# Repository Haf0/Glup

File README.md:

# Glup
Glup is split keyboard 3x6 with 3 thumb cluster that support Choc and MX,and reversible pcb
there's 2 version of glup, big and little glup, big without snapable pcb and little with snappable pcb

why glup? dunno, the name is not fixed but that's the name that I just came out with hehhe

## WARNING!!!!
Untested board, please use it with your own risk!!
and I need to fix the spacing

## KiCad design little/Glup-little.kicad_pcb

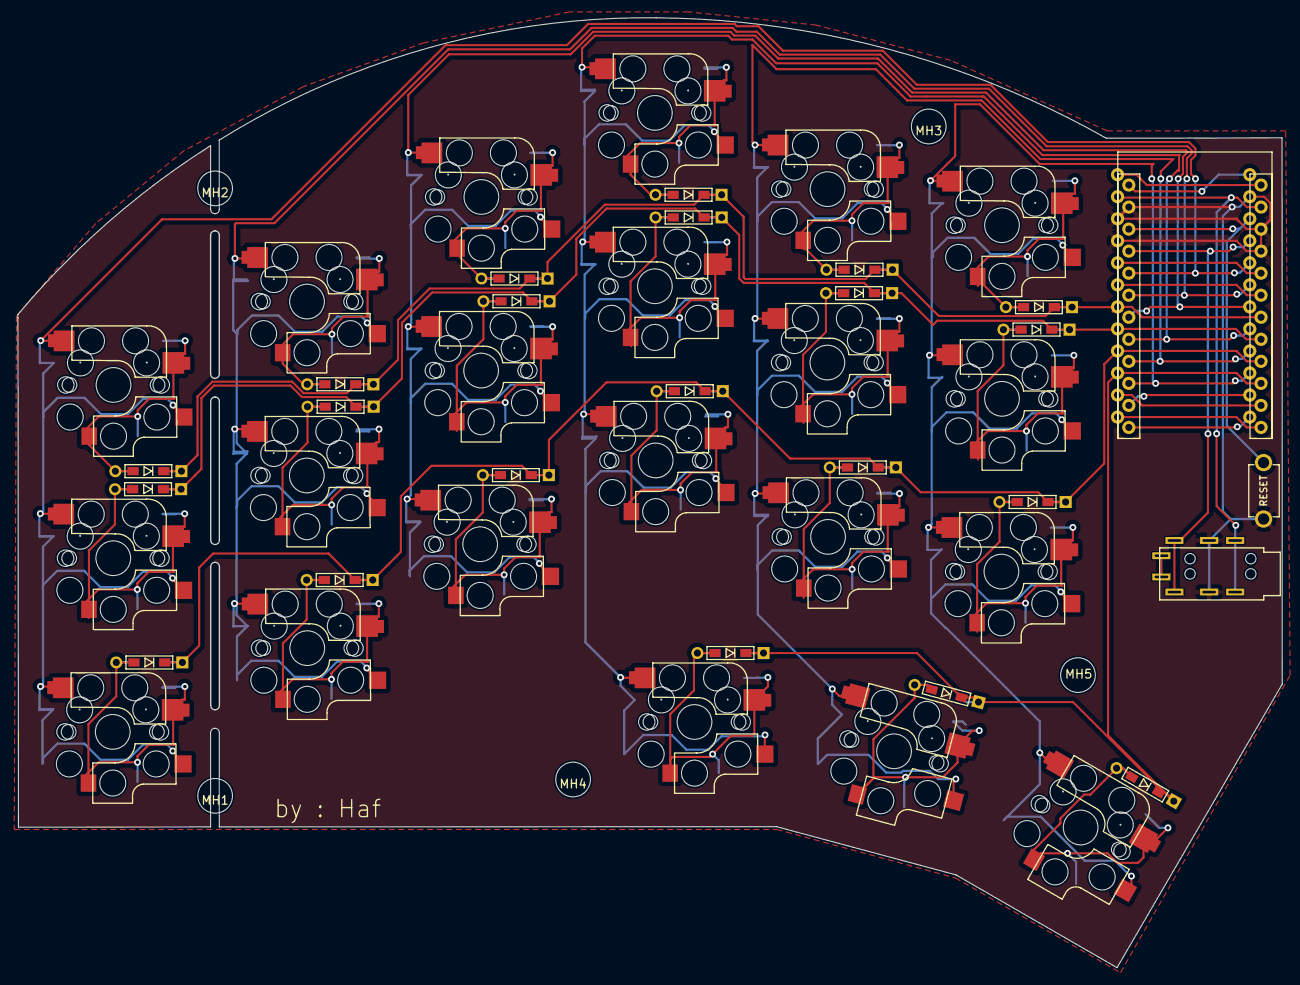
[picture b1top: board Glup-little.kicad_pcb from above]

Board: 2 copper layers, 145.7 x 109.5 mm, 50 parts (0 on the bottom side), 35 nets.

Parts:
D1, D2, D3, D4, D5, D6, D7, D8, D9, D10, D11, D12, D13, D14, D15, D16, D17, D18, D19, D20, D21: D; D3_TH_SMD
J2: MJ-4PP-9; TRRS_JACK_MJ4PP9
MH1, MH2, MH3, MH4, MH5: MOUNT_HOLE; M2_Hole_NPTH_Outside
RSW1: SW_PUSH; TACT_SWITCH_TVBP06
SW1, SW2, SW3, SW4, SW5, SW6, SW7, SW8, SW9, SW10, SW11, SW12, SW13, SW14, SW15, SW16, SW17, SW18, SW19, SW20, SW21: SW_PUSH; MX_Choc_Hotswap
U1: ProMicro; ProMicro_rev2

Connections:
GND: J2.C, RSW1.2, U1.3 (GND), U1.4 (GND), U1.23 (GND)
unnamed: D1.2 (A), SW1.2
unnamed: D2.2 (A), SW2.2
unnamed: D3.2 (A), SW3.2
unnamed: D4.2 (A), SW4.2
unnamed: D5.2 (A), SW5.2
unnamed: D6.2 (A), SW6.2
unnamed: D7.2 (A), SW7.2
unnamed: D8.2 (A), SW8.2
unnamed: D9.2 (A), SW9.2
unnamed: D10.2 (A), SW10.2
unnamed: D11.2 (A), SW11.2
unnamed: D12.2 (A), SW12.2
unnamed: D13.2 (A), SW13.2
unnamed: D14.2 (A), SW14.2
unnamed: D15.2 (A), SW15.2
unnamed: D16.2 (A), SW16.2
unnamed: D17.2 (A), SW17.2
unnamed: D18.2 (A), SW18.2
unnamed: D19.2 (A), SW19.2
unnamed: D20.2 (A), SW20.2
unnamed: D21.2 (A), SW21.2
VCC: J2.D, U1.21 (VCC)
col0: SW1.1, SW2.1, SW3.1, U1.20 (F4/A3)
col1: SW4.1, SW5.1, SW6.1, U1.19 (F5/A2)
col2: SW7.1, SW8.1, SW9.1, U1.18 (F6/A1)
col3: SW10.1, SW11.1, SW12.1, SW13.1, U1.17 (F7/A0)
col4: SW14.1, SW15.1, SW16.1, SW17.1, U1.16 (B1/15)
col5: SW18.1, SW19.1, SW20.1, SW21.1, U1.15 (B3/14)
data: J2.B, U1.2 (RX1/D2)
reset: RSW1.1, U1.22 (RST)
row0: D1.1 (K), D4.1 (K), D7.1 (K), D10.1 (K), D14.1 (K), D18.1 (K), U1.7 (4/D4)
row1: D2.1 (K), D5.1 (K), D8.1 (K), D11.1 (K), D15.1 (K), D19.1 (K), U1.8 (5/C6)
row2: D3.1 (K), D6.1 (K), D9.1 (K), D12.1 (K), D16.1 (K), D20.1 (K), U1.9 (6/D7)
row3: D13.1 (K), D17.1 (K), D21.1 (K), U1.10 (7/E6)

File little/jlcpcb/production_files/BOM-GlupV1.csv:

Comment,Designator,Footprint,LCSC
SW_PUSH,SW9,MX_Choc_Hotswap,
SW_PUSH,SW13,MX_Choc_Hotswap,
D,D14,D3_TH_SMD,
SW_PUSH,RSW1,TACT_SWITCH_TVBP06,
ProMicro,U1,ProMicro_rev2,
D,D16,D3_TH_SMD,
MOUNT_HOLE,MH1,M2_Hole_NPTH_Outside,
MOUNT_HOLE,MH2,M2_Hole_NPTH_Outside,
SW_PUSH,SW6,MX_Choc_Hotswap,
SW_PUSH,SW5,MX_Choc_Hotswap,
D,D11,D3_TH_SMD,
SW_PUSH,SW4,MX_Choc_Hotswap,
D,D20,D3_TH_SMD,
D,D13,D3_TH_SMD,
D,D7,D3_TH_SMD,
D,D1,D3_TH_SMD,
SW_PUSH,SW11,MX_Choc_Hotswap,
SW_PUSH,SW3,MX_Choc_Hotswap,
D,D17,D3_TH_SMD,
MOUNT_HOLE,MH4,M2_Hole_NPTH_Outside,
SW_PUSH,SW20,MX_Choc_Hotswap,
D,D9,D3_TH_SMD,
D,D5,D3_TH_SMD,
SW_PUSH,SW15,MX_Choc_Hotswap,
SW_PUSH,SW8,MX_Choc_Hotswap,
SW_PUSH,SW12,MX_Choc_Hotswap,
D,D19,D3_TH_SMD,
D,D21,D3_TH_SMD,
D,D8,D3_TH_SMD,
MOUNT_HOLE,MH3,M2_Hole_NPTH_Outside,
SW_PUSH,SW2,MX_Choc_Hotswap,
D,D4,D3_TH_SMD,
MOUNT_HOLE,MH5,M2_Hole_NPTH_Outside,
SW_PUSH,SW17,MX_Choc_Hotswap,
D,D10,D3_TH_SMD,
SW_PUSH,SW19,MX_Choc_Hotswap,
D,D12,D3_TH_SMD,
MJ-4PP-9,J2,TRRS_JACK_MJ4PP9,
SW_PUSH,SW18,MX_Choc_Hotswap,
SW_PUSH,SW10,MX_Choc_Hotswap,
SW_PUSH,SW21,MX_Choc_Hotswap,
D,D2,D3_TH_SMD,
D,D18,D3_TH_SMD,
SW_PUSH,SW14,MX_Choc_Hotswap,
D,D3,D3_TH_SMD,
D,D6,D3_TH_SMD,
D,D15,D3_TH_SMD,
SW_PUSH,SW16,MX_Choc_Hotswap,
SW_PUSH,SW7,MX_Choc_Hotswap,
SW_PUSH,SW1,MX_Choc_Hotswap,

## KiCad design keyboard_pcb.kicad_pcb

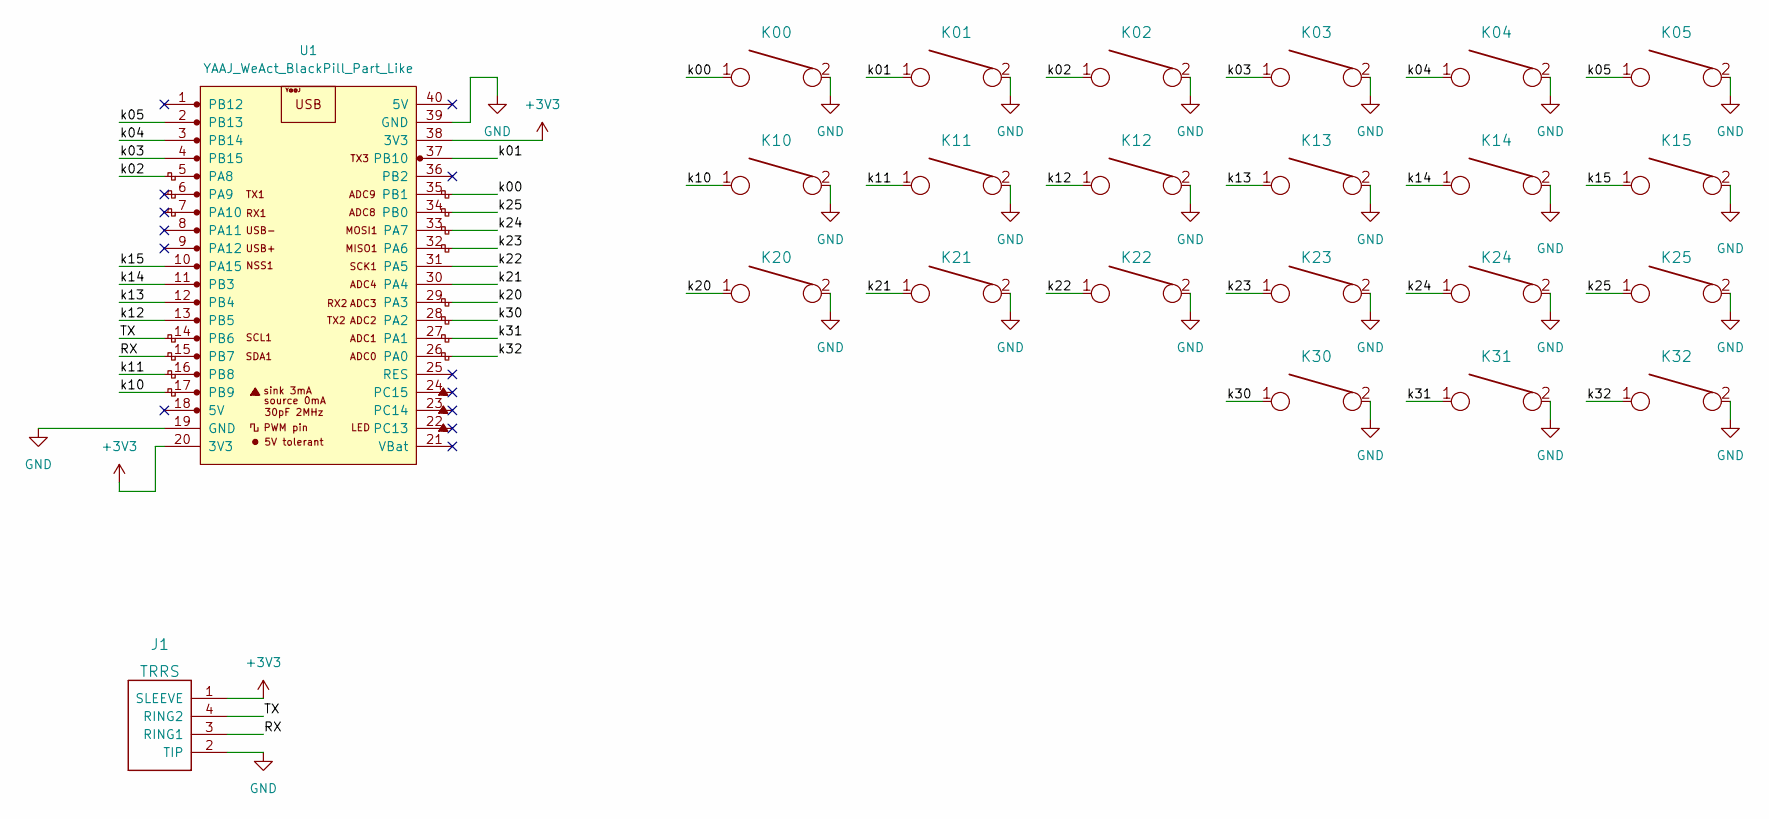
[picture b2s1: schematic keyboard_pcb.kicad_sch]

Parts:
J1: TRRS; TRRS-PJ-320A
K00, K01, K02, K03, K04, K05, K10, K11, K12, K13, K14, K15, K20, K21, K22, K23, K24, K25, K30, K31, K32: KEYSW; MX_Choc_Hotswap_Mod
U1: YAAJ_WeAct_BlackPill_Part_Like; YAAJ_WeAct_BlackPill_2

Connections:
+3V3: J1.1 (SLEEVE), U1.20 (3V3), U1.38 (3V3)
/RX: J1.3 (RING1), U1.15 (PB7)
/TX: J1.4 (RING2), U1.14 (PB6)
/k00: K00.1, U1.35 (PB1)
/k01: K01.1, U1.37 (PB10)
/k02: K02.1, U1.5 (PA8)
/k03: K03.1, U1.4 (PB15)
/k04: K04.1, U1.3 (PB14)
/k05: K05.1, U1.2 (PB13)
/k10: K10.1, U1.17 (PB9)
/k11: K11.1, U1.16 (PB8)
/k12: K12.1, U1.13 (PB5)
/k13: K13.1, U1.12 (PB4)
/k14: K14.1, U1.11 (PB3)
/k15: K15.1, U1.10 (PA15)
/k20: K20.1, U1.29 (PA3)
/k21: K21.1, U1.30 (PA4)
/k22: K22.1, U1.31 (PA5)
/k23: K23.1, U1.32 (PA6)
/k24: K24.1, U1.33 (PA7)
/k25: K25.1, U1.34 (PB0)
/k30: K30.1, U1.28 (PA2)
/k31: K31.1, U1.27 (PA1)
/k32: K32.1, U1.26 (PA0)
GND: J1.2 (TIP), K00.2, K01.2, K02.2, K03.2, K04.2, K05.2, K10.2, K11.2, K12.2, K13.2, K14.2, K15.2, K20.2, K21.2, K22.2, K23.2, K24.2, K25.2, K30.2, K31.2, K32.2, U1.19 (GND), U1.39 (GND)

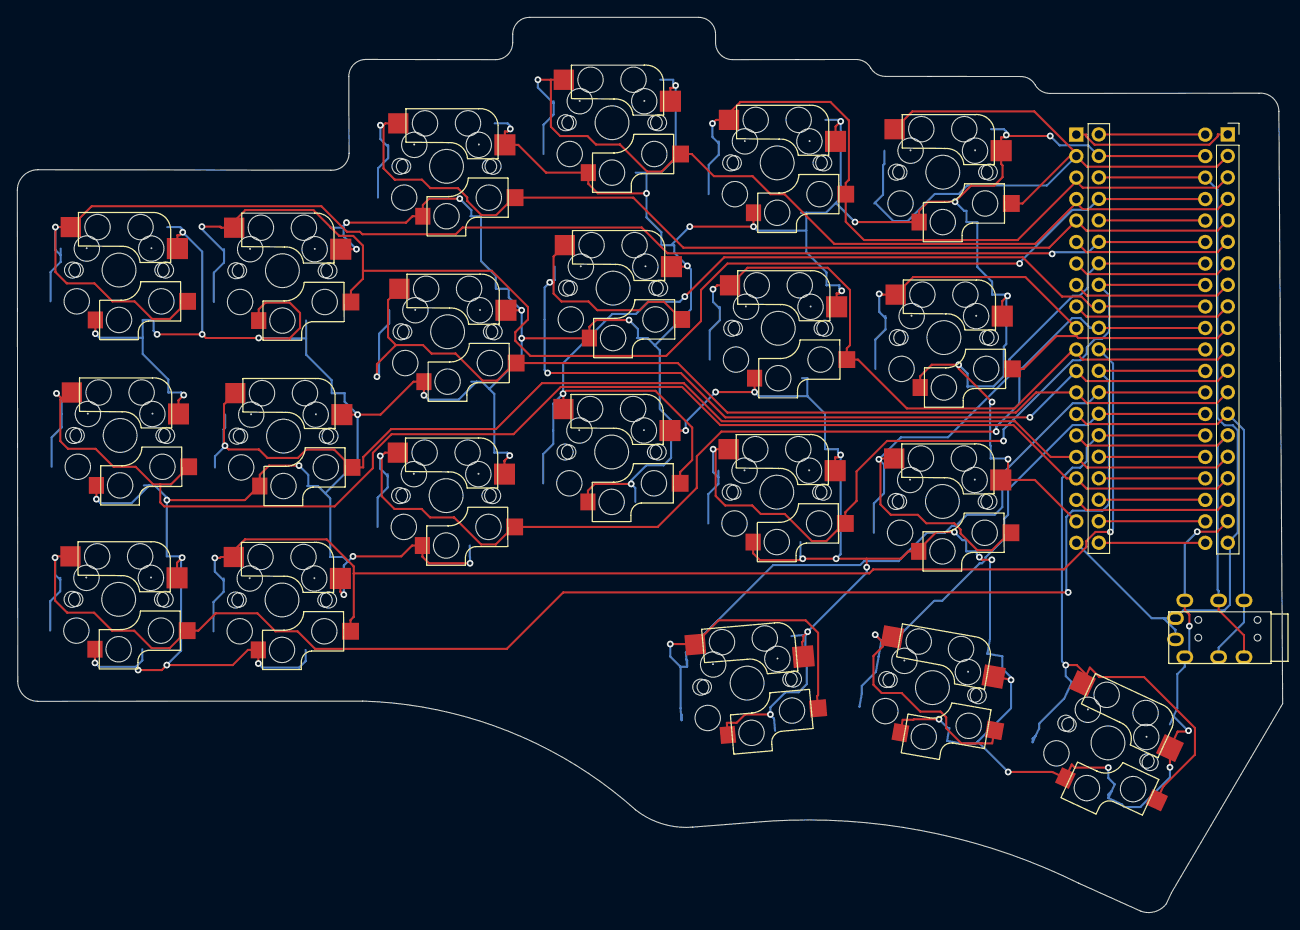
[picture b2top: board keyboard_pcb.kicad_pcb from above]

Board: 2 copper layers, 149.6 x 105.8 mm, 23 parts (0 on the bottom side), 25 nets.

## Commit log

2023-08-11 intial commit
2023-08-21 basically new keyboard
2023-08-21 separate big and little glup
